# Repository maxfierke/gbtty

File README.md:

# gbtty

gbtty (pronounced: _gib-bit-EE_ / "gibbity") is a Game Boy (Color) hardware and
software project to turn the Game Boy into an ANSI-compatible terminal.

# Goals

The primary goal of this project is _funsies_. I wanted to work on a side
project where I could use Rust, play around with an RP2040, and do something
related to my current hyperfixation: the Game Boy.

Secondary goals include providing a useful-enough implementation of an ANSI
terminal, at least to be VT100-compatible to the extent that matters for modern
purposes.

Some stretch goals include supporting a broad set of ANSI escape codes, such as
text/background color on the Game Boy Color, some support for scrollback, and
perhaps even some support for some TUI elements depending on how wild I decide
to get with this.

## Anti-goals

I am not planning on turning this into an interactive terminal accepting input
to be passed back to the host. The only possible way to make this work would be
using some sort of on-screen keyboard control, and I am simply not masochistic
enough to use that.

# Current status

The software side of things is _mostly_ working for basic printing and support
for cursor movement, cursor reporting, and a few other CSI sequences. It's
currently setup to compile and run on the Waveshare RP2040-Zero and configured
to run on [this pico-gb-printer board](https://github.com/Raphael-Boichot/Collection-of-PCB-for-Game-Boy-Printer-Emulators/tree/main#game-boy-printer-emulator-pcb-for-the-waveshare-rp2040-zero)
as I happened to have a couple of these, but should be configurable to run on
other similar boards by remapping the GPIOs & swapping the BSP crate.

The hardware is still a work in-progress. The `pcb/` has a few different v1.0
designs that still need to be tested. The design is more-or-less the same as
other USB-to-link-cable boards out there, but I'm eventually trying to get it as
close as I can to the footprint of a USB-to-UART adapter.

# License

The firmware of the link adapter (contents of the root & `src/` directory) is
licensed under either the [Apache License Version 2.0](LICENSE-APACHE-2-0) or
[The MIT License](LICENSE-MIT)

The PCB (contents of `pcb/`) is licensed under
[Creative Commons Attribution-NonCommercial-ShareAlike 4.0 International](https://creativecommons.org/licenses/by-nc-sa/4.0/). **Commercial uses are strictly prohibited.**

The terminal emulator ROM itself (contents of the `gb/` directory) is derived
from orangeglo's Better Button Test, which is licensed under the [GNU General
Public License Version 3](gb/LICENSE), so the same license applies.

# Disclaimer

Game Boy™ is a trademark of Nintendo of America Inc.

# Useful resources

- [How Terminals Work](https://how-terminals-work.vercel.app/) - Interactive look at how ANSI terminals function (VT100 and xterm derivatives especially)
- [vt100.net/emu/](https://vt100.net/emu/) - Paul Flo Williams' tome on terminal emulation
- [Everything you never wanted to know about ANSI escape codes](https://notes.burke.libbey.me/ansi-escape-codes/)

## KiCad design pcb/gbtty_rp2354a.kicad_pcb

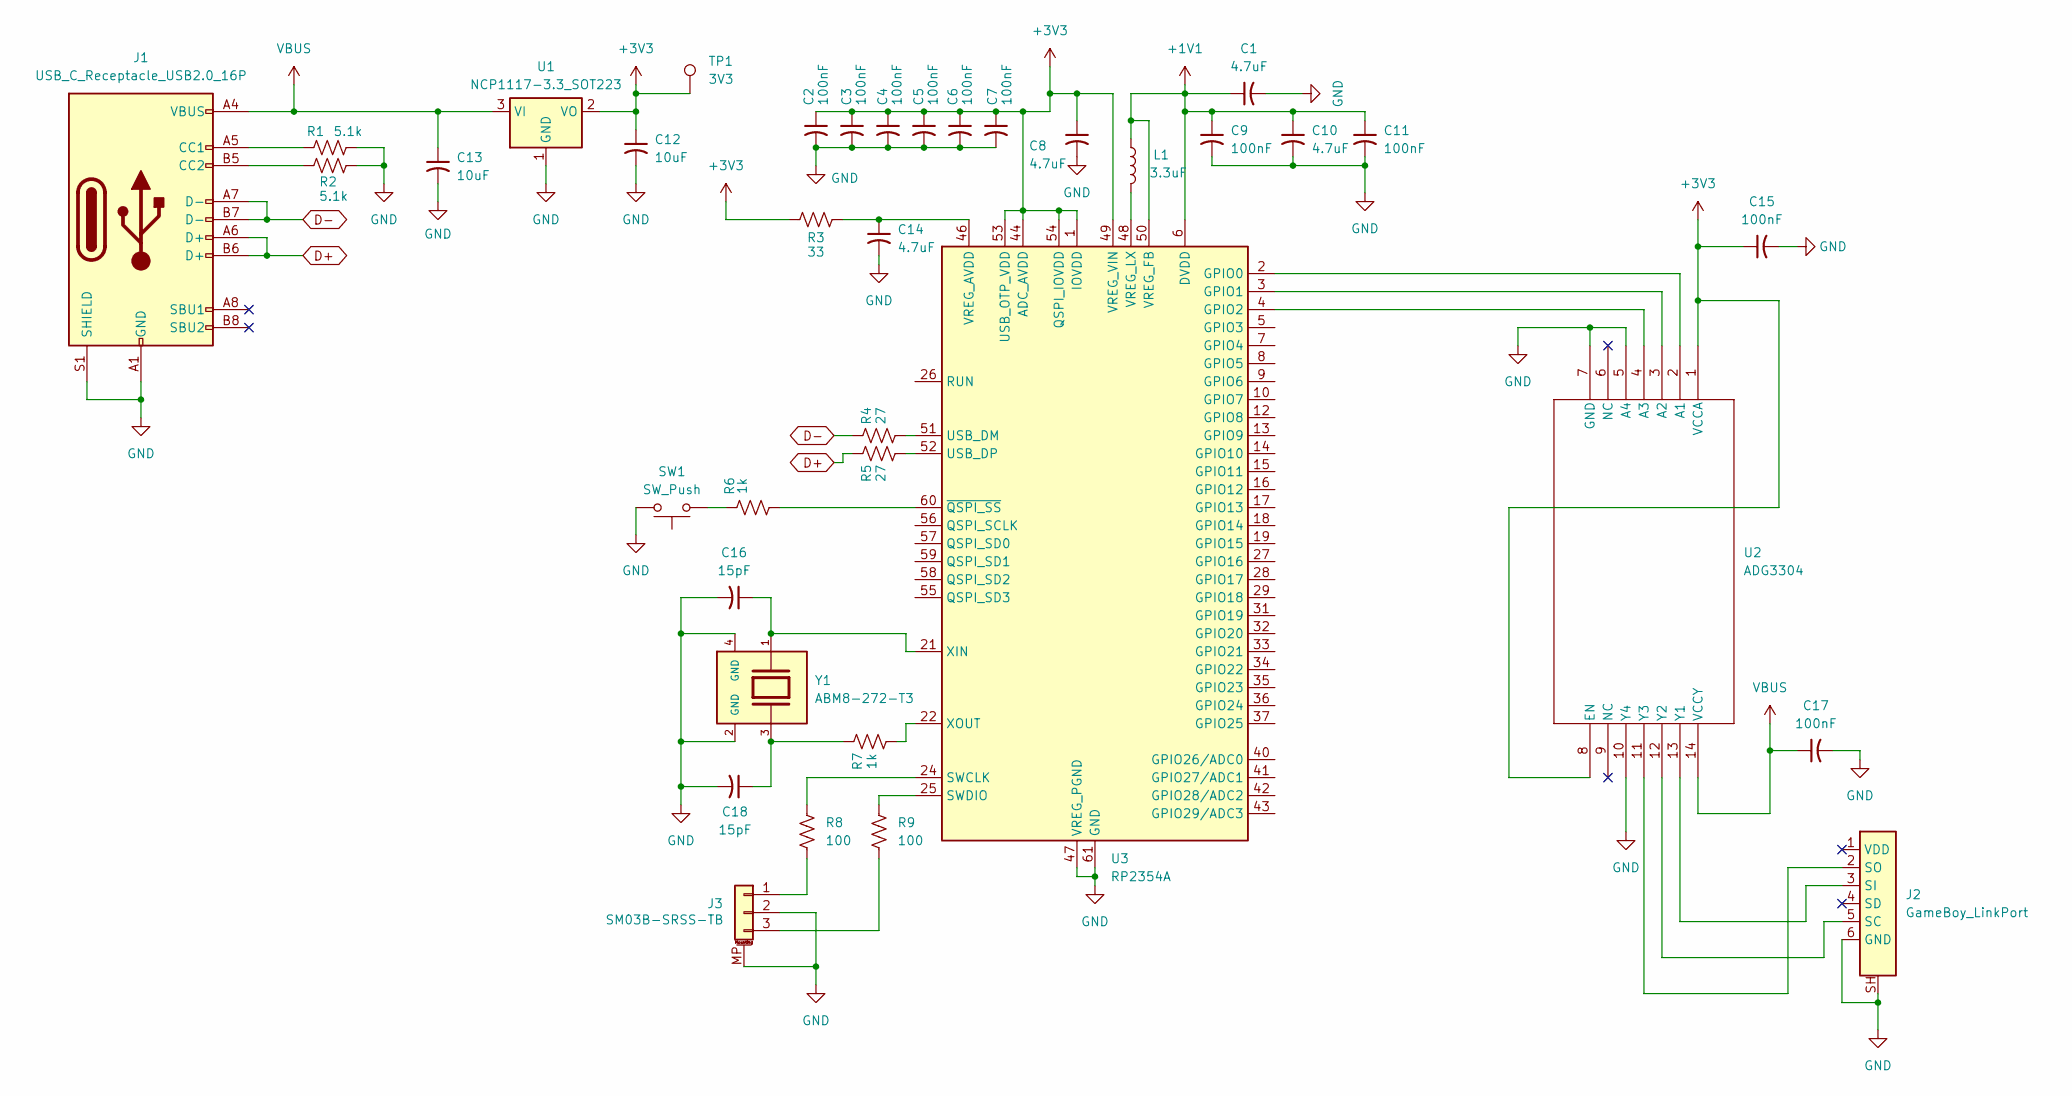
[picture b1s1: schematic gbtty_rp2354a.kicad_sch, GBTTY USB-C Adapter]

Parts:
C1, C8, C10, C14: 4.7uF; C_0603_1608Metric_Pad1.08x0.95mm_HandSolder
C2, C3, C4, C5, C6, C7, C9, C11, C15, C17: 100nF; C_0603_1608Metric_Pad1.08x0.95mm_HandSolder
C12, C13: 10uF; C_0603_1608Metric_Pad1.08x0.95mm_HandSolder
C16, C18: 15pF; C_0603_1608Metric_Pad1.08x0.95mm_HandSolder
J1: USB_C_Receptacle_USB2.0_16P; USB_C_Receptacle_GCT_USB4105-xx-A_16P_TopMnt_Horizontal
J2: GameBoy_LinkPort; GameBoy_LinkPort_MGB_Horizontal
J3: SM03B-SRSS-TB; JST_SH_BM03B-SRSS-TB_1x03-1MP_P1.00mm_Vertical
L1: 3.3uF; L_pol_2016
R1, R2: 5.1k; R_0603_1608Metric_Pad0.98x0.95mm_HandSolder
R3: 33; R_0603_1608Metric_Pad0.98x0.95mm_HandSolder
R4, R5: 27; R_0603_1608Metric_Pad0.98x0.95mm_HandSolder
R6, R7: 1k; R_0603_1608Metric_Pad0.98x0.95mm_HandSolder
R8, R9: 100; R_0603_1608Metric_Pad0.98x0.95mm_HandSolder
SW1: SW_Push; SW_SPST_TL3305A
TP1: 3V3; TestPoint_Pad_D1.0mm
U1: NCP1117-3.3_SOT223; SOT-223-3_TabPin2
U2: ADG3304; RU_14_ADI
U3: RP2354A; QFN-60-1EP_7x7mm_P0.4mm_EP3.4x3.4mm
Y1: ABM8-272-T3; XTAL_ABM8-272-T3; PARTREV 07-29-20

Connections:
+1V1: C1.1, C9.1, C10.1, C11.1, L1.1, U3.6 (DVDD), U3.23 (DVDD), U3.39 (DVDD), U3.50 (VREG_FB)
+3V3: C2.1, C3.1, C4.1, C5.1, C6.1, C7.1, C8.1, C12.1, C15.1, R3.2, TP1.1, U1.2 (VO), U2.1 (VCCA), U2.8 (EN), U3.1 (IOVDD), U3.11 (IOVDD), U3.20 (IOVDD), U3.30 (IOVDD), U3.38 (IOVDD), U3.44 (ADC_AVDD), U3.45 (IOVDD), U3.49 (VREG_VIN), U3.53 (USB_OTP_VDD), U3.54 (QSPI_IOVDD)
D+: J1.A6 (D+), J1.B6 (D+), R5.1
D-: J1.A7 (D-), J1.B7 (D-), R4.1
GND: C1.2, C2.2, C3.2, C4.2, C5.2, C6.2, C7.2, C8.2, C9.2, C10.2, C11.2, C12.2, C13.2, C14.2, C15.2, C16.2, C17.2, C18.2, J1.A1 (GND), J1.A12 (GND), J1.B1 (GND), J1.B12 (GND), J1.S1 (SHIELD), J2.6 (GND), J2.SH, J3.2, J3.MP (MountPin), R1.2, R2.2, SW1.2, U1.1 (GND), U2.5 (A4), U2.7 (GND), U2.10 (Y4), U3.47 (VREG_PGND), U3.61 (GND), Y1.2 (GND), Y1.4 (GND)
unnamed: C18.1, R7.1, Y1.3
unnamed: J1.A5 (CC1), R1.1
unnamed: J1.B5 (CC2), R2.1
unnamed: J2.5 (SC), U2.12 (Y2)
unnamed: J2.3 (SI), U2.13 (Y1)
unnamed: J2.2 (SO), U2.11 (Y3)
unnamed: J3.1, R8.2
unnamed: J3.3, R9.2
unnamed: R6.1, SW1.1
unnamed: U2.2 (A1), U3.2 (GPIO0)
unnamed: U2.3 (A2), U3.3 (GPIO1)
unnamed: U2.4 (A3), U3.4 (GPIO2)
unnamed: R8.1, U3.24 (SWCLK)
unnamed: R9.1, U3.25 (SWDIO)
unnamed: R4.2, U3.51 (USB_DM)
unnamed: R5.2, U3.52 (USB_DP)
unnamed: C14.1, R3.1, U3.46 (VREG_AVDD)
unnamed: L1.2, U3.48 (VREG_LX)
unnamed: C16.1, U3.21 (XIN), Y1.1
unnamed: R7.2, U3.22 (XOUT)
unnamed: R6.2, U3.60 (~QSPI_SS)
VBUS: C13.1, C17.1, J1.A4 (VBUS), J1.A9 (VBUS), J1.B4 (VBUS), J1.B9 (VBUS), U1.3 (VI), U2.14 (VCCY)

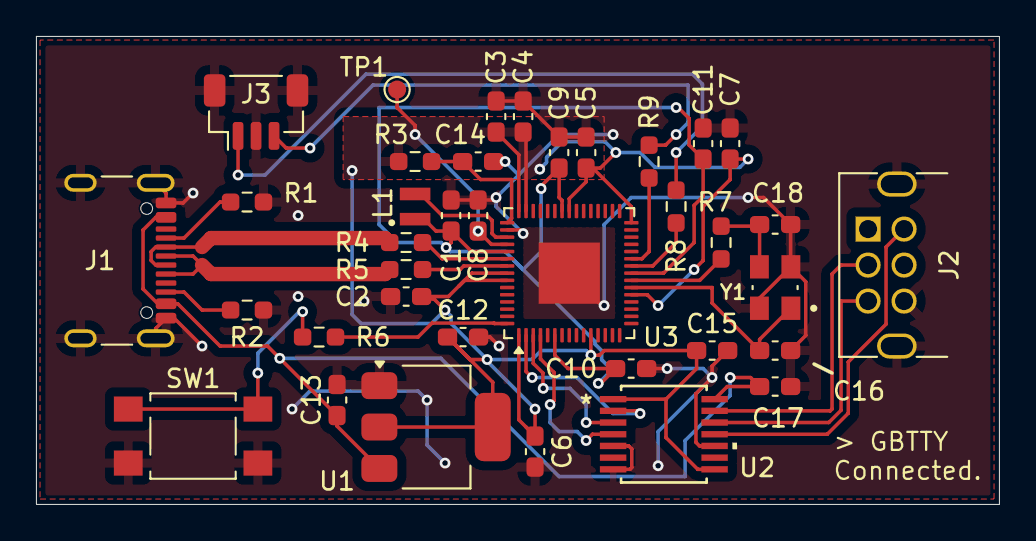
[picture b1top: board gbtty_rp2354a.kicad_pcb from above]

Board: 2 copper layers, 53.5 x 26.0 mm, 37 parts (0 on the bottom side), 27 nets.

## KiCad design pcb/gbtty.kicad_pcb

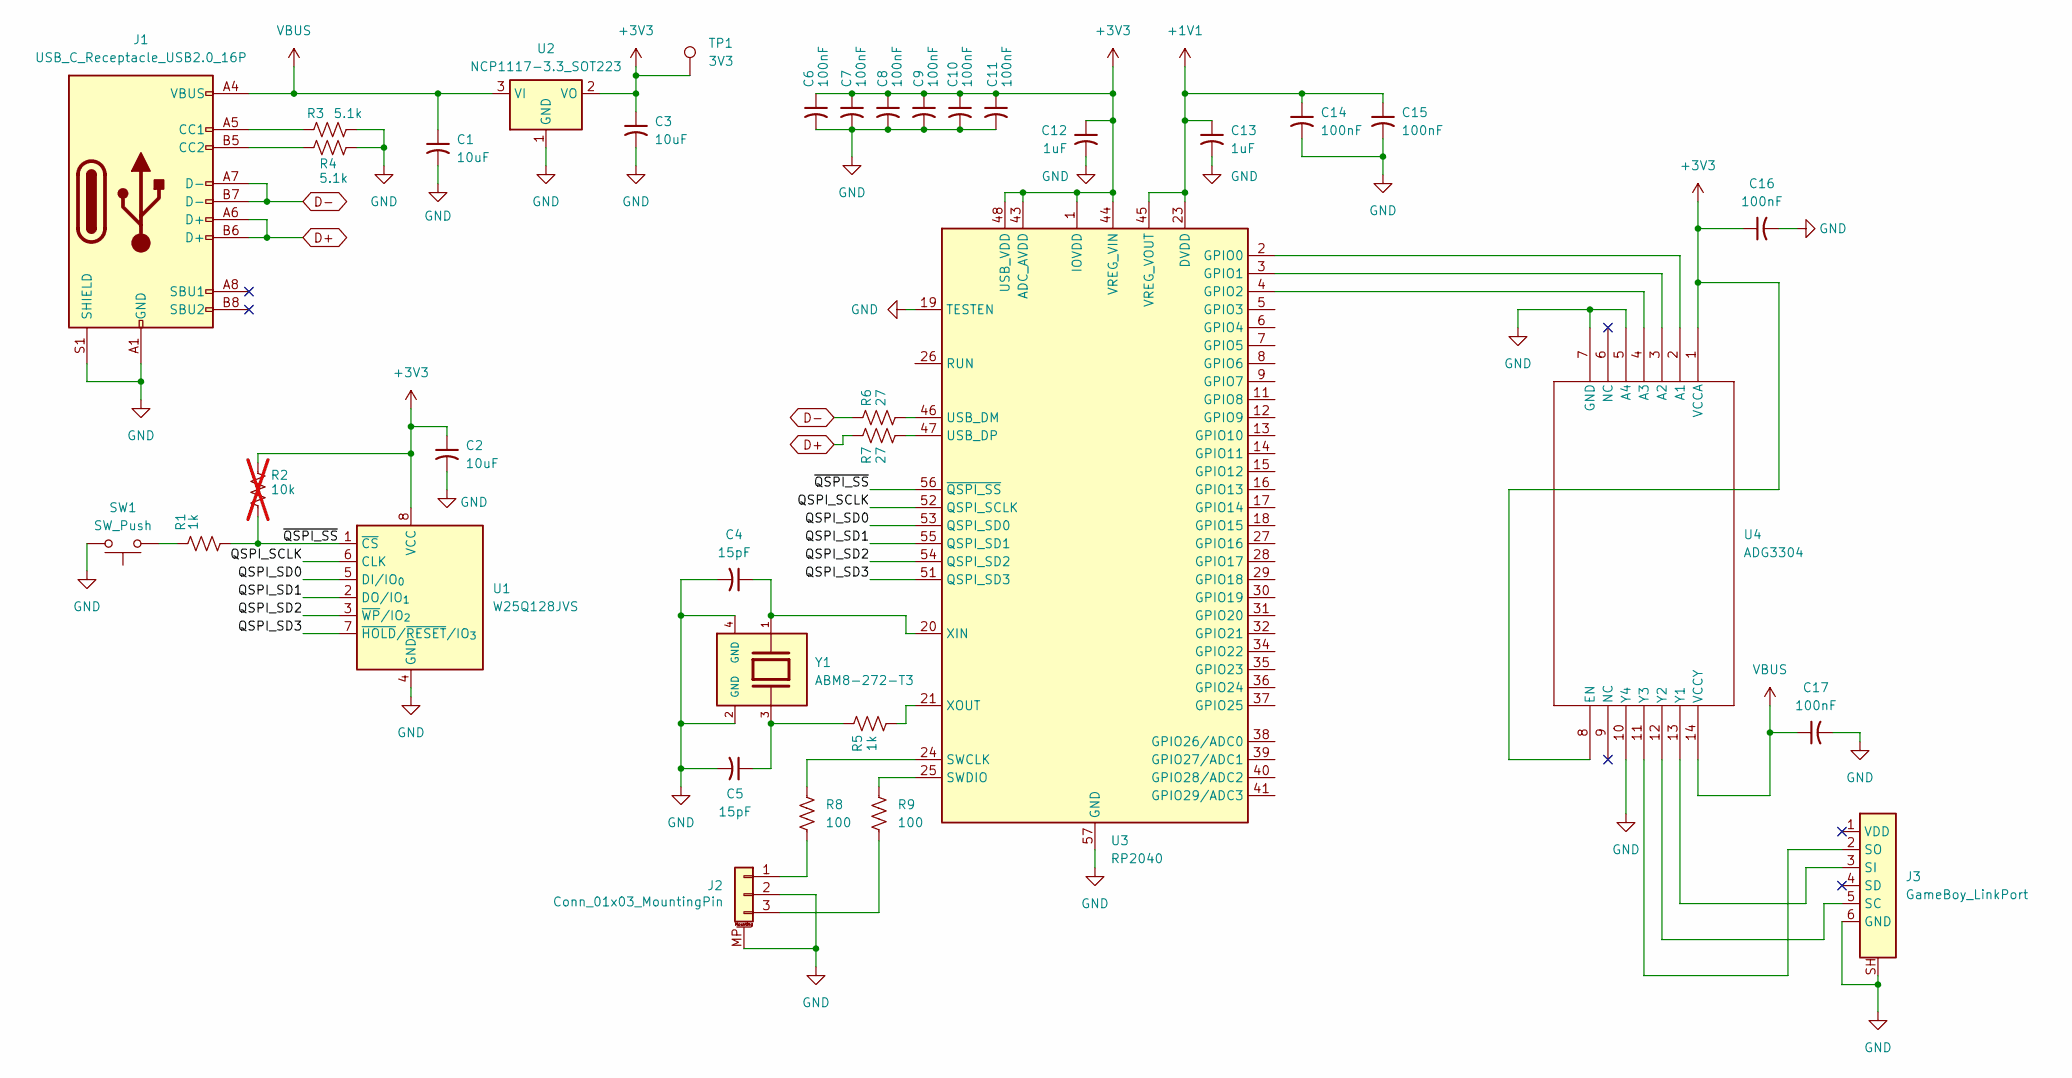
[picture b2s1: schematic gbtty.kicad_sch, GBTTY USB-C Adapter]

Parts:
C1, C2, C3: 10uF; C_0603_1608Metric_Pad1.08x0.95mm_HandSolder
C4, C5: 15pF; C_0603_1608Metric_Pad1.08x0.95mm_HandSolder
C6, C7, C8, C9, C10, C11, C14, C15, C16, C17: 100nF; C_0603_1608Metric_Pad1.08x0.95mm_HandSolder
C12, C13: 1uF; C_0603_1608Metric_Pad1.08x0.95mm_HandSolder
J1: USB_C_Receptacle_USB2.0_16P; USB_C_Receptacle_GCT_USB4105-xx-A_16P_TopMnt_Horizontal
J2: Conn_01x03_MountingPin; JST_SH_BM03B-SRSS-TB_1x03-1MP_P1.00mm_Vertical
J3: GameBoy_LinkPort; GameBoy_LinkPort_MGB_Horizontal
R1, R5: 1k; R_0603_1608Metric_Pad0.98x0.95mm_HandSolder
R2: 10k; R_0603_1608Metric_Pad0.98x0.95mm_HandSolder; not fitted
R3, R4: 5.1k; R_0603_1608Metric_Pad0.98x0.95mm_HandSolder
R6, R7: 27; R_0603_1608Metric_Pad0.98x0.95mm_HandSolder
R8, R9: 100; R_0603_1608Metric_Pad0.98x0.95mm_HandSolder
SW1: SW_Push; SW_SPST_TL3305A
TP1: 3V3; TestPoint_Pad_D1.0mm
U1: W25Q128JVS; SOIC-8_5.3x5.3mm_P1.27mm
U2: NCP1117-3.3_SOT223; SOT-223-3_TabPin2
U3: RP2040; QFN-56-1EP_7x7mm_P0.4mm_EP3.2x3.2mm
U4: ADG3304; RU_14_ADI
Y1: ABM8-272-T3; XTAL_ABM8-272-T3; PARTREV 07-29-20

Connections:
+1V1: C13.1, C14.1, C15.1, U3.23 (DVDD), U3.45 (VREG_VOUT), U3.50 (DVDD)
+3V3: C2.1, C3.1, C6.1, C7.1, C8.1, C9.1, C10.1, C11.1, C12.1, C16.1, R2.1, TP1.1, U1.8 (VCC), U2.2 (VO), U3.1 (IOVDD), U3.10 (IOVDD), U3.22 (IOVDD), U3.33 (IOVDD), U3.42 (IOVDD), U3.43 (ADC_AVDD), U3.44 (VREG_VIN), U3.48 (USB_VDD), U3.49 (IOVDD), U4.1 (VCCA), U4.8 (EN)
/QSPI_SCLK: U1.6 (CLK), U3.52 (QSPI_SCLK)
/QSPI_SD0: U1.5 (DI/IO_{0}), U3.53 (QSPI_SD0)
/QSPI_SD1: U1.2 (DO/IO_{1}), U3.55 (QSPI_SD1)
/QSPI_SD2: U1.3 (~WP/IO_{2}), U3.54 (QSPI_SD2)
/QSPI_SD3: U1.7 (~HOLD/~RESET/IO_{3}), U3.51 (QSPI_SD3)
/~QSPI_SS: R1.2, R2.2, U1.1 (~CS), U3.56 (~QSPI_SS)
D+: J1.A6 (D+), J1.B6 (D+), R7.1
D-: J1.A7 (D-), J1.B7 (D-), R6.1
GND: C1.2, C2.2, C3.2, C4.2, C5.2, C6.2, C7.2, C8.2, C9.2, C10.2, C11.2, C12.2, C13.2, C14.2, C15.2, C16.2, C17.2, J1.A1 (GND), J1.A12 (GND), J1.B1 (GND), J1.B12 (GND), J1.S1 (SHIELD), J2.2, J2.MP (MountPin), J3.6 (GND), J3.SH, R3.2, R4.2, SW1.2, U1.4 (GND), U2.1 (GND), U3.19 (TESTEN), U3.57 (GND), U4.5 (A4), U4.7 (GND), U4.10 (Y4), Y1.2 (GND), Y1.4 (GND)
unnamed: C5.1, R5.1, Y1.3
unnamed: J1.A5 (CC1), R3.1
unnamed: J1.B5 (CC2), R4.1
unnamed: J2.1, R8.2
unnamed: J2.3, R9.2
unnamed: J3.5 (SC), U4.12 (Y2)
unnamed: J3.3 (SI), U4.13 (Y1)
unnamed: J3.2 (SO), U4.11 (Y3)
unnamed: R1.1, SW1.1
unnamed: U3.2 (GPIO0), U4.2 (A1)
unnamed: U3.3 (GPIO1), U4.3 (A2)
unnamed: U3.4 (GPIO2), U4.4 (A3)
unnamed: R8.1, U3.24 (SWCLK)
unnamed: R9.1, U3.25 (SWDIO)
unnamed: R6.2, U3.46 (USB_DM)
unnamed: R7.2, U3.47 (USB_DP)
unnamed: C4.1, U3.20 (XIN), Y1.1
unnamed: R5.2, U3.21 (XOUT)
VBUS: C1.1, C17.1, J1.A4 (VBUS), J1.A9 (VBUS), J1.B4 (VBUS), J1.B9 (VBUS), U2.3 (VI), U4.14 (VCCY)

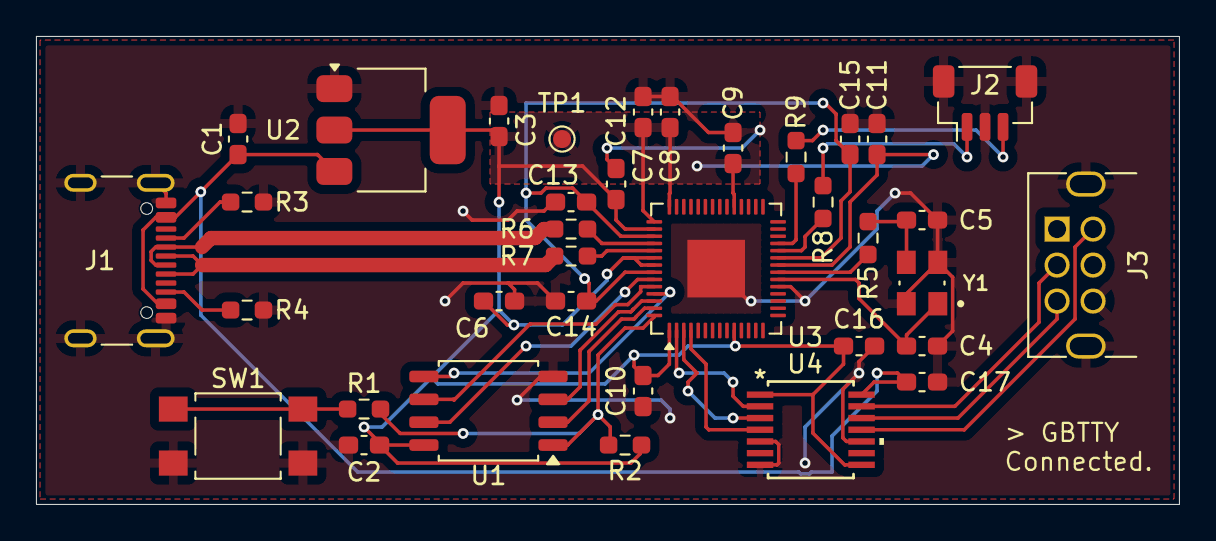
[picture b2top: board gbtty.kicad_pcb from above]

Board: 2 copper layers, 63.5 x 26.0 mm, 36 parts (0 on the bottom side), 30 nets.

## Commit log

2025-12-26 gb: Import a very barebones GB rom based on better-button-test
2025-12-30 gb: barebones dumb terminal
    Not much supported. Basic ASCII set supported by the built-in GBDK IBM font. Unprintable characters skipped. Functioning newlines, backspace, and wrapping.
2025-12-30 gb: Add a link indicator to more clearly indicate when stuff is happening
2026-01-11 rp: add first pass of RP firmware
    Link port leader mode implemented via PIO, basic USB serial stack w/ echo and link port forwarding
2026-01-11 rp: use heapless queue instead of shared-mem-queue
2026-01-19 gb: refactor term implemention to support CSI cursor and screen clearing, decouple link receciving from rendering
2026-01-19 rp: fix multi-byte writes
2026-01-19 rp: appease clippy
2026-01-19 gb: decouple terminal state from rendering
2026-01-22 gb: increase link buffer size to 128 bytes
    This seems to help with avoiding overflow situations
    w/ programmatic output.
2026-01-22 rp: drop PIO clock to ~262kHz for 32KB/s data rate
    While 500 kHz does work to some degree it is simply too fast
    for the GB to keep up with in normal-speed mode if the buffer
    is constantly full. Will revisit when exploring double-speed later
2026-01-22 gb: enable the gbdk compat for ACK when GBDK_DEBUG set
    This is mostly just useful in testing in emulators against test roms using GBDK's built-in send_byte/receive_byte. They have their own semantics for indicating idle, sending, receiving state that nee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
    be matched for communication to work.
2026-02-27 pcb: Add initial pcb design
2026-02-27 pcb: Add alt RP2354A pcb design
    This also hasn't been validated yet either, and is probably more
    likely to need changes.
2026-02-27 pcb: Put the rp2354a design in the shrink-ray
2026-02-27 pcb: Update generated BOM pages
2026-02-27 rp: Customize pins for rp-pico
2026-02-27 gb: implement cursor navigation with arrow keys, fix CSI arg parsing
2026-02-27 gb: implement CSI 5n, CSI 6n, and limited CSI c and CSI m support
    Cursor reporting is implemented, along with inverse graphics, and
    a (probably) erroneous CSI c support.
2026-02-27 rp: read back from link port and forward to host
2026-02-27 Add current status to README
2026-02-27 rp: remove erroneous shift on link port read
    this was what I get for basing this off a UART implementation
2026-03-07 rp: address some linter feedback
2026-03-07 gb: make dev target compatible with *nix
2026-03-09 gb: extract terminal & link port bits to seperate source files
    Just trying to make this a little more managable
2026-03-09 Update current status in README
2026-03-09 gb: move term state global vars into structs
2026-03-09 gb: move palettes out to their own header
2026-03-09 gb: fix make dev on macOS
2026-03-09 gb: add script for testing CSI sequences
2026-03-10 gb: actually finish implementing CSI n K
    apparantly I had just copied CSI n J and forgot to modify it, oops
2026-03-10 Add some useful resources to the README
2026-03-12 gb: (mostly) move off gbdk font system
    Still using `font_load` and `font_color` to load fonts initially, but that's it.
    In addition, switched to using font_ibm_fixed, which seems to supported extended ASCII.
    Unfortunately, this leaves us with no room for other fonts, but that's okay.
2026-03-13 gb: add sprite based cursor for DMG/MGB
    This seems to be the easiest way to do an invert here -- not sure how we'll do this for terminal cells, but less concerned with that.
2026-03-17 gb: fix row/col being swapped in term_clear_cell
2026-03-17 gb: fix inverse being improperly applied following refactor
2026-03-17 gb: update test script to write out test content prior to cursor reporting
2026-03-19 gb: swap in oldschool-cga-8x8, a cp437 font
    This removes the last use of the gbdk font system.
    It's not my favorite font, so this is likely a stop gap for a bit,
    as its close to font_ibm_fixed
2026-03-19 rp: bump rust to 1.94
2026-03-20 gb: replace oldschool-cga-8x8 with portfolio
2026-03-21 gb: put link port writes in a critical section, mark ring buffers volatile
2026-03-21 gb: term_state_t -> term_t

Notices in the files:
pcb/gbtty.kicad_pcb:
License: Creative Commons Attribution-NonCommercial-ShareAlike 4.0 International
(c) 2026 Max Fierke
Licensed under CC-BY-NC 4.0
